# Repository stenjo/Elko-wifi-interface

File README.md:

# Elko-wifi-interface
Need to get my ELKO Living system wifi enabled so that I can detect and control changes and usage.

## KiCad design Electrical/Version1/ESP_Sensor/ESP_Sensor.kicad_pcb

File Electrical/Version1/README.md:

# Electrical Design

### **!!NOTE!!**
The more mature version of a HAN Port reader is available under the folder [HAN_ESP_TSS721](../HAN_ESP_TSS721). The main difference in these two versions are that this one is using a proprietary (but simpler) circuit for the M-bus to TTL
conversion and has very limited resources available for doing work on the schematics and PCB. The [HAN_ESP_TSS721](../HAN_ESP_TSS721) is using a TSS721 circuit
from Texas Instruments, specifically designed for M-bus to TTL conversion. Also
all design is available for you in a [KiCad](https://www.kicad-pcb.org) format.

## Explained
The design is using an opamp as a compined level converter and a schmitt trigger, in order to convert 
the HAN signal into a 3.3V compatible serial format. As the input levels on the opamp is much higher 
than our 5V supply, we are rectifying and smoothing the HAN signal to use for a supply here. (VDD)

As a power source, we've used a micro USB connector, providing 5V, just as this is cheap and easy. However,
no part of the circuit will need any other power than the 3.3V, so any combination of power source and 
regulator that provides the 3.3V will do.

The ESP8266 setup is a rather standaraized setup and will allow for programming the ESP directly on the 
board, if needed. During programming, it might be neccessary to disconnect the incoming HAN.

### **!!important changes!!**
> * R8 should not be used
> * The two unused inputs on the LM358 should be grounded (Pin 5 and 6)

## Schematics

## PCB

## Componenet list
Name | Value | Part
-----|------|-----
C1|10uF/25V|[P5148-ND](https://www.digikey.no/product-detail/en/panasonic-electronic-components/ECA-1EM100/P5148-ND/245007)
C2|100nF|[BC1101CT-ND](https://www.digikey.no/product-detail/en/vishay-bc-components/K104K10X7RF5UH5/BC2665CT-ND/2356879)
C3|220uF/35V|[1572-1706-ND](https://www.digikey.no/product-detail/en/illinois-capacitor/227CKS035M/1572-1706-ND/5411729)
D1|1N4148|[1N4148FS-ND](https://www.digikey.no/product-detail/en/fairchild-on-semiconductor/1N4148/1N4148FS-ND/458603)
P1||[609-4613-1-ND](https://www.digikey.no/product-detail/en/amphenol-fci/10118192-0001LF/609-4613-1-ND/2785378)
P2|Female|[S7004-ND](https://www.digikey.no/product-detail/en/sullins-connector-solutions/PPTC061LFBN-RC/S7004-ND/810145)
P3|Male|[952-2262-ND](https://www.digikey.no/product-detail/en/harwin-inc/M20-9990246/952-2262-ND/3728226)
P4||[609-1047-ND](https://www.digikey.no/product-detail/en/amphenol-fci/54602-910LF/609-1047-ND/1001361)
Q1|BC337|[BC33725TACT-ND](https://www.digikey.no/product-detail/en/fairchild-on-semiconductor/BC33725TA/BC33725TACT-ND/1532787)
R1-5,10,11|10K|[CF14JT10K0CT-ND](https://www.digikey.no/product-detail/en/stackpole-electronics-inc/CF14JT10K0/CF14JT10K0CT-ND/1830374)
R8|100K|[CF14JT100KCT-ND](https://www.digikey.no/product-detail/en/stackpole-electronics-inc/CF14JT100K/CF14JT100KCT-ND/1830399)
R9|330R|[CF14JT330RCT-ND](https://www.digikey.no/product-detail/en/stackpole-electronics-inc/CF14JT330R/CF14JT330RCT-ND/1830338)
R12,13|47K|[CF14JT47K0CT-ND](https://www.digikey.no/product-detail/en/stackpole-electronics-inc/CF14JT47K0/CF14JT47K0CT-ND/1830391)
S1,2||[450-1650-ND](https://www.digikey.no/product-detail/en/te-connectivity-alcoswitch-switches/1825910-6/450-1650-ND/1632536)
U2|LM1117-3.3|[LM1117IMPX-3.3/NOPBCT-ND](https://www.digikey.no/product-detail/en/texas-instruments/LM1117IMPX-3.3-NOPB/LM1117IMPX-3.3-NOPBCT-ND/3440160)
U3|LM358|[LM358NGOS-ND](https://www.digikey.no/product-detail/en/on-semiconductor/LM358NG/LM358NGOS-ND/918519)

Note: The ESP8266 is not included here. It can easily be found on ebay etc

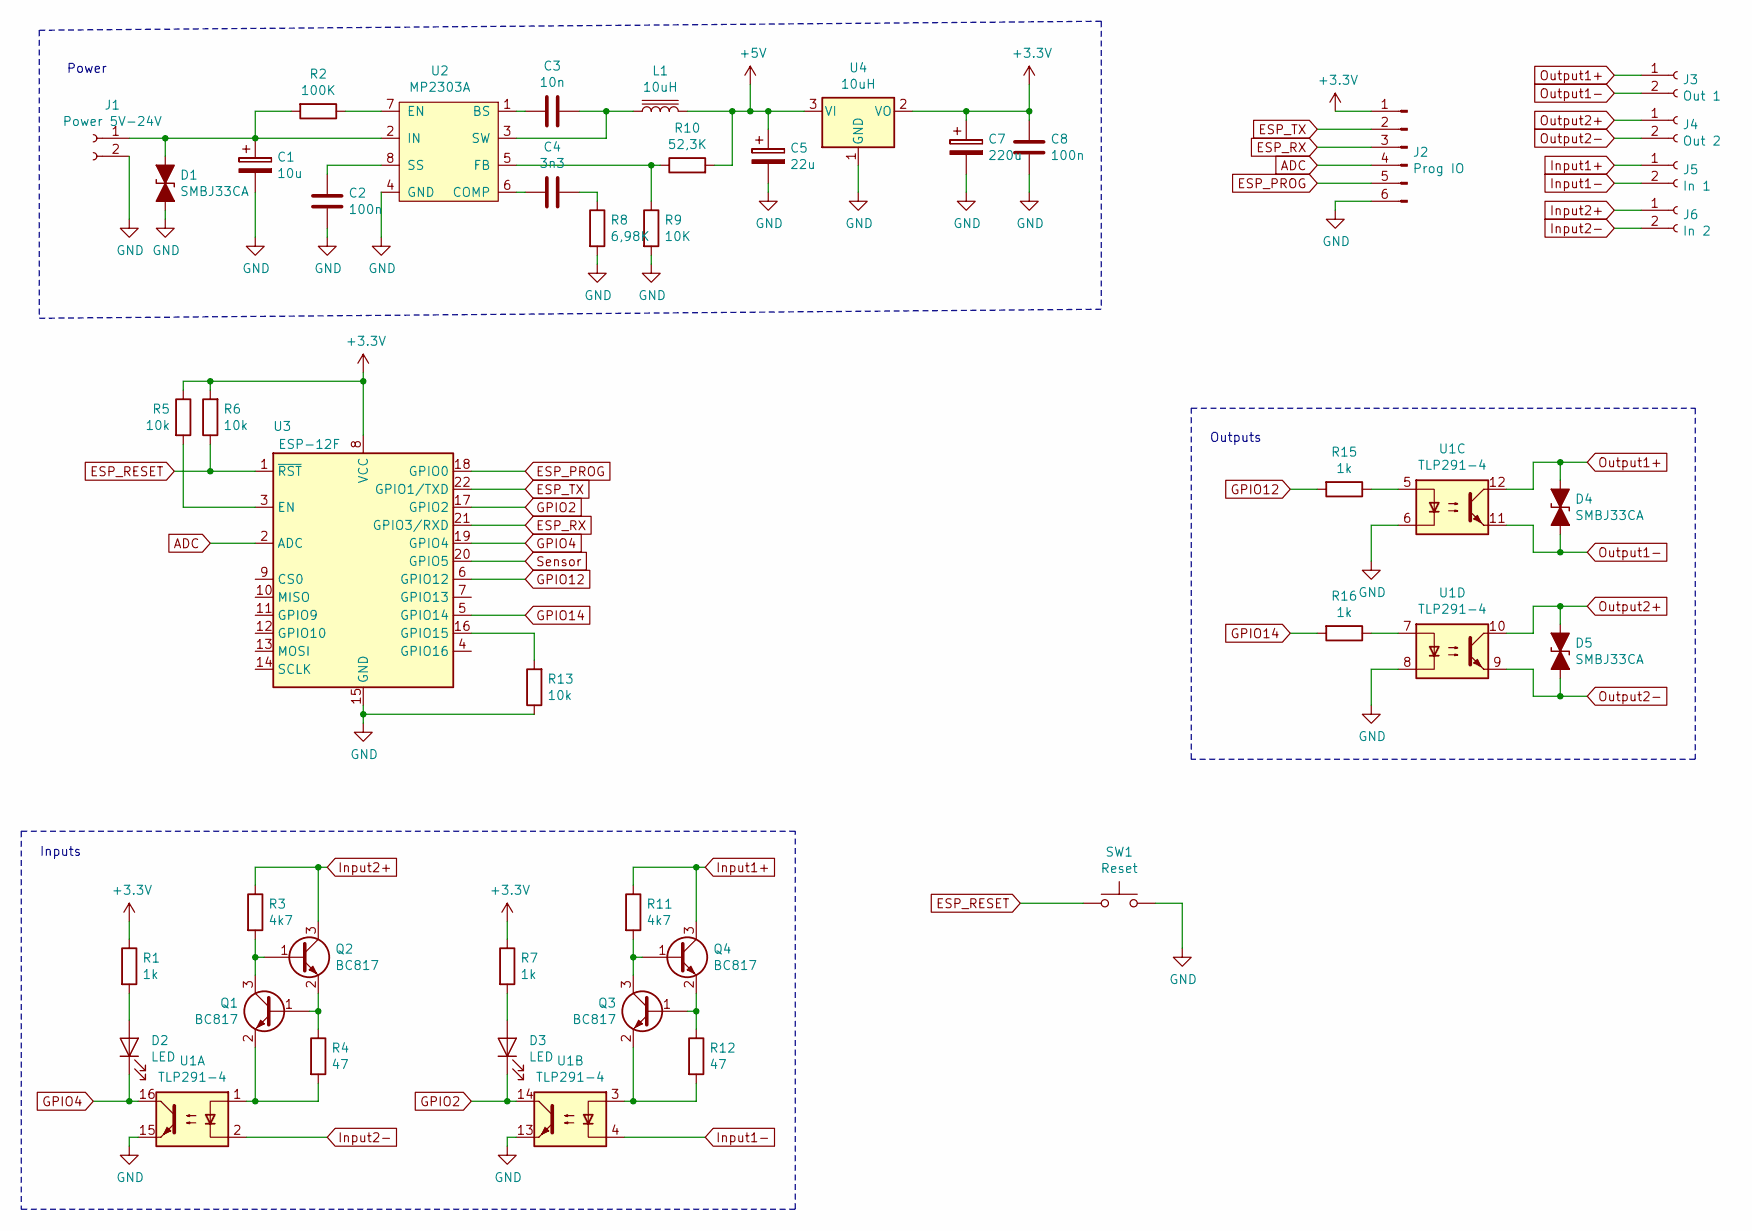
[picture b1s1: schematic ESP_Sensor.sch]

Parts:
C1: 10u; CP_Radial_D5.0mm_P2.00mm
C2, C8: 100n; C_0805_2012Metric_Pad1.15x1.40mm_HandSolder
C3: 10n; C_0805_2012Metric_Pad1.15x1.40mm_HandSolder
C4: 3n3; C_0805_2012Metric_Pad1.15x1.40mm_HandSolder
C5: 22u; CP_Radial_D5.0mm_P2.00mm
C7: 220u; CP_Radial_D6.3mm_P2.50mm
D1, D4, D5: SMBJ33CA; D_SMA-SMB_Universal_Handsoldering
D2, D3: LED; LED_0805_2012Metric_Pad1.15x1.40mm_HandSolder
J1: Power 5V-24V; TerminalBlock_Phoenix_MKDS-1,5-2_1x02_P5.00mm_Horizontal
J2: Prog IO; PinHeader_1x06_P2.54mm_Vertical
J3: Out 1; TerminalBlock_Phoenix_MKDS-1,5-2_1x02_P5.00mm_Horizontal
J4: Out 2; TerminalBlock_Phoenix_MKDS-1,5-2_1x02_P5.00mm_Horizontal
J5: In 1; TerminalBlock_Phoenix_MKDS-1,5-2_1x02_P5.00mm_Horizontal
J6: In 2; TerminalBlock_Phoenix_MKDS-1,5-2_1x02_P5.00mm_Horizontal
L1: 10uH; CD43
Q1, Q2, Q3, Q4: BC817; SOT-23
R1, R7, R15, R16: 1k; R_0805_2012Metric_Pad1.15x1.40mm_HandSolder
R2: 100K; R_0805_2012Metric_Pad1.15x1.40mm_HandSolder
R3, R11: 4k7; R_0805_2012Metric_Pad1.15x1.40mm_HandSolder
R4, R12: 47; R_0805_2012Metric_Pad1.15x1.40mm_HandSolder
R5, R6, R13: 10k; R_0805_2012Metric_Pad1.15x1.40mm_HandSolder
R8: 6,98K; R_0805_2012Metric_Pad1.15x1.40mm_HandSolder
R9: 10K; R_0805_2012Metric_Pad1.15x1.40mm_HandSolder
R10: 52,3K; R_0805_2012Metric_Pad1.15x1.40mm_HandSolder
SW1: Reset; SW_PUSH_6mm_H7.3mm
U1: TLP291-4; SOIC-16_4.55x10.3mm_P1.27mm
U2: MP2303A; SOIC-8_3.9x4.9mm_P1.27mm
U3: ESP-12F; ESP-12E
U4: 10uH; SOT-223-3_TabPin2

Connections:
+3V3: C7.1, C8.1, J2.1, R1.1, R5.1, R6.2, R7.1, U3.8 (VCC), U4.2 (VO)
+5V: C5.1, L1.2, R10.2, U4.3 (VI)
ADC: J2.4, U3.2 (ADC)
ESP_PROG: J2.5, U3.18 (GPIO0)
ESP_RESET: R6.1, SW1.1, U3.1 (~RST)
ESP_RX: J2.3, U3.21 (GPIO3/RXD)
ESP_TX: J2.2, U3.22 (GPIO1/TXD)
GND: C1.2, C2.1, C5.2, C7.2, C8.2, D1.2 (A2), J1.2, J2.6, R8.2, R9.2, R13.1, SW1.2, U1.6, U1.8, U1.13, U1.15, U2.4 (GND), U3.15 (GND), U4.1 (GND)
GPIO2: D3.1 (K), U1.14, U3.17 (GPIO2)
GPIO4: D2.1 (K), U1.16, U3.19 (GPIO4)
GPIO12: R15.2, U3.6 (GPIO12)
GPIO14: R16.2, U3.5 (GPIO14)
Input1+: J5.1, Q4.3 (C), R11.1
Input1-: J5.2, U1.4
Input2+: J6.1, Q2.3 (C), R3.1
Input2-: J6.2, U1.2
unnamed: C1.1, D1.1 (A1), J1.1, R2.2, U2.2 (IN)
unnamed: C2.2, U2.8 (SS)
unnamed: C3.1, L1.1, U2.3 (SW)
unnamed: C3.2, U2.1 (BS)
unnamed: C4.1, R8.1
unnamed: C4.2, U2.6 (COMP)
unnamed: D2.2 (A), R1.2
unnamed: D3.2 (A), R7.2
unnamed: Q1.1 (B), Q2.2 (E), R4.1
unnamed: Q1.2 (E), R4.2, U1.1
unnamed: Q1.3 (C), Q2.1 (B), R3.2
unnamed: Q3.1 (B), Q4.2 (E), R12.1
unnamed: Q3.2 (E), R12.2, U1.3
unnamed: Q3.3 (C), Q4.1 (B), R11.2
unnamed: R2.1, U2.7 (EN)
unnamed: R5.2, U3.3 (EN)
unnamed: R9.1, R10.1, U2.5 (FB)
unnamed: R13.2, U3.16 (GPIO15)
unnamed: R15.1, U1.5
unnamed: R16.1, U1.7
Output1+: D4.1 (A1), J3.1, U1.12
Output1-: D4.2 (A2), J3.2, U1.11
Output2+: D5.1 (A1), J4.1, U1.10
Output2-: D5.2 (A2), J4.2, U1.9
Sensor: U3.20 (GPIO5)

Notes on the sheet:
Inputs
Outputs
Power

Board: 2 copper layers, 43 parts (12 on the bottom side), 40 nets, no tracks yet.

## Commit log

2019-04-04 Updated pcb board with smd caps
